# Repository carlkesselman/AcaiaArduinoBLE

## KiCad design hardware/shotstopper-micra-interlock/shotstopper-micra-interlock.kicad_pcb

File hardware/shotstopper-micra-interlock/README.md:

# ShotStopper Micra Interlock

A replacement for the ShotStopper V2.1 board, designed to give a La Marzocco
Linea Micra Linea Mini-style brew-by-weight:

- Paddle **on**: the shot starts, and the scale tares and starts its timer.
- Target weight reached: the shot **stops even though the paddle is still on**.
- Paddle **off** at any time: the shot stops, as on a stock machine.
- After an automatic stop, the next shot needs the paddle turned off and on again.
- If the board is unpowered, unplugged from the scale, or crashed, the paddle
  works exactly like a stock Micra.

Status: **design only.** The board has not been built and the firmware has
not run on hardware. Work through [Before you order](#before-you-order) first.

## Same as V2.1

The outline, the four M3 mounting holes, the Arduino Nano ESP32 position, the
two 2x8 ribbon headers (J3 "Buttons", J4 "Brain") and the 2-pin power header
are all where they are on V2.1, so the board fits the V2.1 half case and the
same place in the machine. The ribbon headers have the same pin 1 position
and every pin except the paddle pin passes straight through, so the existing
ShotStopper ribbon cables plug in the same way.

Changed from V2.1: the Nano is soldered directly into the board by its own
headers instead of sitting in sockets. That puts its top about 8 mm lower,
roughly 5–6 mm above the board instead of about 13 mm. It is still flashed
over its own USB-C port, at the board edge marked USB, or over WiFi.

Removed from V2.1: the spade terminals, the reed-switch header, and the Q1
optocoupler circuit. D9 and D11 are no longer connected.

## How it works

```
 J3 paddle pin ──JP1── PADDLE ───[ K1 normally-closed ]─── BRAIN ──JP2── J4 paddle pin
                         │                                             (to control board)
                         └──|<── D1 ── U2 LED ── R3 ── ISO 5V ┐
                                      (R6 across LED)          PS1 isolated DC-DC
 J3/J4 pin 6 (COMMON) ─────────────────────────────── ISO 0V ┘   3.3 V → 5 V
                                                                     (R4 min load)
 Nano D5  ── R1 ── K1 LED            HIGH = K1 open = machine sees paddle off
          └─ R2 10k to GND           keeps K1 closed during boot / reset
 Nano D10 ── U2 transistor to GND    LOW = paddle on  (R7 47k pull-up)
```

- **K1** (CPC1117N) is a normally-closed solid-state switch in series with the
  paddle line. Driving D5 high opens it, so the control board sees the paddle
  as off and stops the shot. With no drive, it is closed.
- **U2** senses the paddle independently of K1. A small isolated 5 V supply
  (PS1) pushes about 1.7 mA through U2's LED and D1 into the paddle wire. When
  the paddle shorts that wire to COMMON, U2 conducts and pulls D10 low. This
  works with K1 open or closed, so the firmware always knows where the paddle is.
- **D1** stops the control board's own pull-up from feeding back into the sense
  circuit. **R6** (680 Ω, smaller than R3) soaks up the leakage when the
  control board's pull-up is about 3.3 V, so a floating line doesn't read as
  "paddle on".
- **R4** (240 Ω, 1206) draws 21 mA so that PS1 has its 10 % minimum load. With
  less, its output is unspecified and can rise well above 5 V.
- The logic side (Nano) and the machine side (ribbon) share no copper. They
  connect only through K1, U2 and PS1. The minimum copper gap between the two
  sides is 0.7 mm. That is **functional isolation for a low-voltage paddle
  line, not mains-rated isolation.**

D10 has the same meaning as V2.1's "In", so the sensing is compatible.
V2.1's parallel "Out" (D11) is not on this board. The old latching mode
(`MOMENTARY false`, `PADDLE_INTERLOCK false`) still runs, but it can no longer
keep a shot going after the paddle is turned off.

## Setting the jumpers (one time, before installing)

V2.1 carried the paddle signal on ribbon pin **8** or pin **12**, depending on
the machine (its SB1–SB5 jumpers). Find out which pin yours uses, either from
your V2.1 board (which of SB1/SB2 is bridged) or with a meter. The ShotStopper
V3.1 schematic puts the Micra on pin 12 and the Linea Mini on pin 8. Then bridge
these with a blob of solder:

| Paddle on | JP1 (paddle side) | JP2 (brain side) | Also bridge |
|-----------|-------------------|------------------|-------------|
| pin 8     | centre to **8**   | centre to **8**  | JP4 (pin 12 straight through) |
| pin 12    | centre to **12**  | centre to **12** | JP3 (pin 8 straight through) |

The "8" and "12" marks are printed at the ends of JP1 and JP2. All other
ribbon pins pass straight through, and pin 6 is COMMON, as on V2.1.

## Firmware

In `examples/shotStopper/shotStopper.ino` set:

```c
#define MOMENTARY false
#define PADDLE_INTERLOCK true
```

What the firmware does in this mode:

| Event | Result |
|-------|--------|
| Paddle on | Machine brews; the shot is tracked: tare, reset and start the timer |
| Predicted target weight, or `MAX_SHOT_DURATION_S` | D5 high: K1 opens and the shot stops |
| Paddle still on after the stop | K1 stays open; no new shot |
| Paddle off (50 ms debounce, `PADDLE_DEBOUNCE_MS`) | D5 low: K1 closes, so the next paddle-on always brews |
| Paddle off before the target | Shot stops; K1 never opens |
| Scale lost during a weighed shot | D5 high: the shot stops (`STOP_ON_SCALE_LOSS`; set it `false` to leave the shot to the paddle) |
| Scale not connected when the paddle goes on | K1 stays closed; the paddle works by hand |
| Paddle on for `INTERLOCK_MAX_BREW_S` (90 s), with or without a scale | D5 high: the brew stops until the paddle is off |
| Reconnect, or reset, partway through a shot | The shot keeps running on the paddle and isn't re-tared |
| Crash or watchdog reset during a held stop | The stop stays held until the paddle is off, so a finished shot isn't restarted |
| `loop()` stalls for 20 s (`WATCHDOG_S`) | The watchdog resets the board, and K1 closes |

### Fail-safe guarantees

- **Paddle off always stops brewing.** This is enforced by hardware: K1 is in
  series, so an open paddle opens the line whatever the ESP32 does.
- **Board unpowered, unplugged, or held in reset.** K1 is normally closed, and R2
  keeps it closed while D5 is undriven, so the Micra behaves as stock.
- **Paddle on starts brewing** whenever the firmware is running, or the board is
  off or resetting. The only time it doesn't is an automatic stop being held,
  and that hold ends as soon as the paddle reads off. A hung ESP32 is reset by
  the watchdog within `WATCHDOG_S`.
- **No remote start.** The ESP32 can only interrupt the paddle line. It cannot
  make the machine brew.

These cases are covered by host tests with stub libraries, not on hardware.

Flow rate, the scale sanity checks and over-the-air updates are described
in [`examples/shotStopper/README.md`](../../examples/shotStopper/README.md).

## Ordering from PCBWay

Everything is in `fab/`:

| File | Upload as |
|------|-----------|
| `shotstopper-micra-interlock-gerbers.zip` | PCB Gerber files (includes drill files) |
| `bom.csv` | Assembly BOM (manufacturer part numbers) |
| `centroid.csv` | Pick-and-place / centroid file (mm, top side) |

PCB options: 2 layers, 44.3 × 41.3 mm, 1.6 mm FR-4, 1 oz copper, any
solder-mask colour, lead-free HASL or ENIG. Minimum track and gap are
0.25 mm and 0.2 mm, and the smallest drill is 0.3 mm (vias), all inside
PCBWay's standard capability.

Assembly: top side only, SMD and through-hole. The Arduino Nano ESP32 *with
headers* (Arduino ABX00092) is on the BOM as J1: PCBWay solders its two pin
rows straight into the J1 and J2 holes, with no sockets, USB-C toward the
edge marked USB. J2 is the Nano's second row, not a separate part, so it is
not on the BOM or in the centroid file. JP1–JP4 are bare pads with no part
to place.

## Before you order

1. **Paddle line voltage and current.** With the machine on, measure DC volts
   between the paddle ribbon wire and pin 6 (COMMON), with the paddle off; expect
   3.3–5 V. Then measure the current with the paddle on; expect a few mA. K1 is
   rated 60 V / 120 mA. The line must not be mains.
2. **Which ribbon pin** carries the paddle (8 or 12). See the jumper table above.
3. **PS1 pinout.** The footprint assumes the industry-standard SIP-4 (1 = Vin−,
   2 = Vin+, 3 = Vout−, 4 = Vout+), which Mornsun B0305S-1WR3 and Murata MEE1S0305SC
   both use. Check it against the current datasheet.
4. **Clearance.** PS1 is about 10 mm tall and sits beside J4 (bottom right).
   Check that it clears whatever is above the board in your machine.
5. **First power-up on the bench.** With only USB connected, check that D5 high
   makes K1 open: measure the resistance between J3 and J4 on the selected pin.
   Then check that shorting the selected J3 pin to pin 6 pulls D10 low.
   Measure across C2 as well: expect 5.0–5.5 V from PS1.

Work inside the Micra only with it unplugged. Mains is present in the chassis.

## Regenerating the board

`design.py` is the source of truth: parts, positions, nets, and the
logic/machine routing areas.

```bash
./make_all.sh /path/to/python-with-numpy-scipy-pillow
```

The script runs `build_board.py` (KiCad Python: places the parts),
`route.py` (a small two-layer router that keeps each net on its own side),
`finish_board.py` (adds tracks and silkscreen), KiCad DRC, and the
Gerber/drill/BOM/centroid exports. It needs KiCad 10. You can open
`shotstopper-micra-interlock.kicad_pcb` in KiCad and edit it by hand, but a
rerun of the script overwrites it.

There is no schematic file. The netlist is in `design.py` (`NETS`).

Based on ShotStopper V2.1 by Tate Mazer (MIT License).

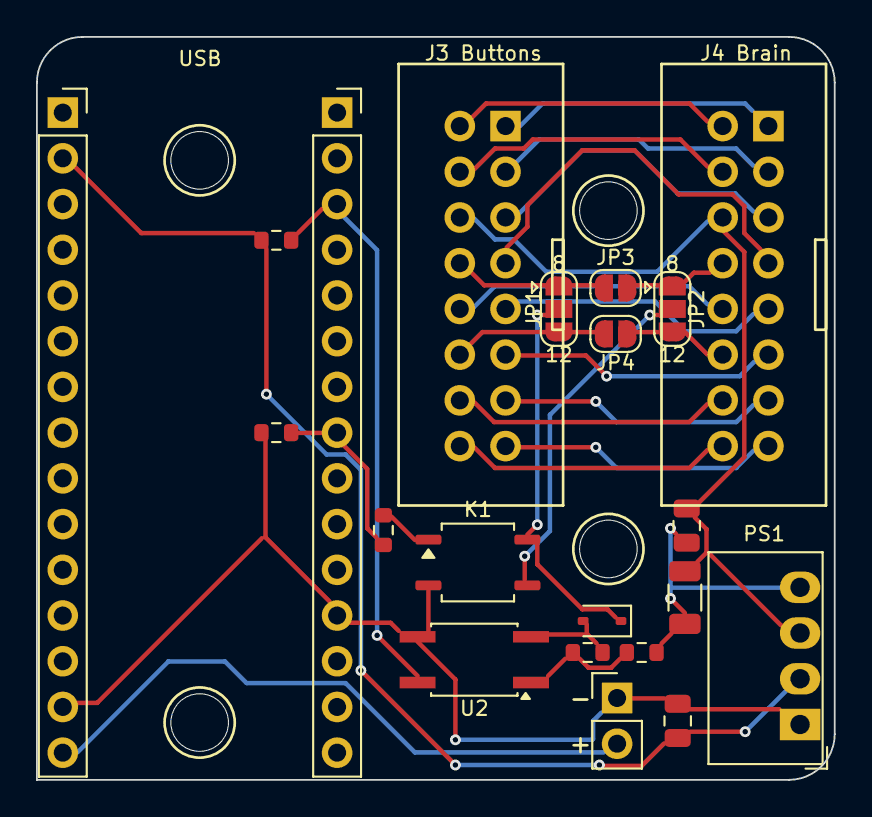
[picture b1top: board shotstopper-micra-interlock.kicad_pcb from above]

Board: 2 copper layers, 44.3 x 41.3 mm, 25 parts (0 on the bottom side), 29 nets.

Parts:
C1, C2: 4.7u; C_0805_2012Metric
D1: 1N4148WS; D_SOD-323
H1, H2, H3, H4: MountingHole_3.2mm_M3_Standoff
J1: Nano ESP32; PinSocket_1x15_P2.54mm_Vertical
J2: Nano ESP32 R row; PinSocket_1x15_P2.54mm_Vertical
J3: Buttons; Ribbon_2x08_P2.54mm_V2.1
J4: Brain; Ribbon_2x08_P2.54mm_V2.1
J5: PWR; PinHeader_1x02_P2.54mm_Vertical
JP1: PADDLE 8|12; SolderJumper-3_P1.3mm_Open_RoundedPad1.0x1.5mm
JP2: BRAIN 8|12; SolderJumper-3_P1.3mm_Open_RoundedPad1.0x1.5mm
JP3: 8 THRU; SolderJumper-2_P1.3mm_Open_RoundedPad1.0x1.5mm
JP4: 12 THRU; SolderJumper-2_P1.3mm_Open_RoundedPad1.0x1.5mm
K1: CPC1117N; SOP-4_3.8x4.1mm_P2.54mm
PS1: B0305S-1WR3; Converter_DCDC_Murata_MEE1SxxxxSC_THT
R1: 390; R_0603_1608Metric
R2: 10k; R_0603_1608Metric
R3: 1k; R_0603_1608Metric
R4: 240; R_1206_3216Metric
R6: 680; R_0603_1608Metric
R7: 47k; R_0603_1608Metric
U2: EL357N; SO-4_4.4x3.6mm_P2.54mm

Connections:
+3V3: C1.1, J1.2, PS1.2, R7.1
BRAIN: JP2.2, K1.3
COMMON: C2.2, J3.6, J4.6, PS1.3, R4.2
GND: C1.2, J1.14, J2.12, J5.1, K1.2, PS1.1, R2.1, U2.3
ISO5V: C2.1, PS1.4, R3.2, R4.1
K1_A: K1.1, R1.2
PADDLE: D1.1, JP1.2, K1.4
RIB1: J3.1, J4.1
RIB2: J3.2, J4.2
RIB3: J3.3, J4.3
RIB4: J3.4, J4.4
RIB5: J3.5, J4.5
RIB7: J3.7, J4.7
RIB8_B: J4.8, JP2.1, JP3.2
RIB8_P: J3.8, JP1.1, JP3.1
RIB9: J3.9, J4.9
RIB10: J3.10, J4.10
RIB11: J3.11, J4.11
RIB12_B: J4.12, JP2.3, JP4.2
RIB12_P: J3.12, JP1.3, JP4.1
RIB13: J3.13, J4.13
RIB14: J3.14, J4.14
RIB15: J3.15, J4.15
RIB16: J3.16, J4.16
SENSE: J2.3, R7.2, U2.4
STOP: J2.8, R1.1, R2.2
U2_A: R3.1, R6.1, U2.1
U2_K: D1.2, R6.2, U2.2
VIN: J1.15, J5.2

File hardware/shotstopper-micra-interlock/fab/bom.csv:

Item,Designator,Qty,Manufacturer,Mfg Part #,Description / Value,Package/Footprint,Type,Notes
1,J1,1,Arduino,ABX00092,Nano ESP32 - Arduino Nano ESP32 with headers (left pin row; right row in J2),PinSocket_1x15_P2.54mm_Vertical,Thru-hole,"One module, two pin rows: J1 = left row (pin 1 = D13), J2 = right row (pin 1 = D12). USB-C toward the board edge marked USB. Solder the Nano's headers directly into J1 and J2, seated flat; NO sockets"
2,J3,1,Sullins,PEC08DAAN,Buttons - Male header 2x8 2.54mm (paddle ribbon),Ribbon_2x08,Thru-hole,Mount on TOP side
3,J4,1,Sullins,PEC08DAAN,Brain - Male header 2x8 2.54mm (control board ribbon),Ribbon_2x08,Thru-hole,
4,J5,1,Sullins,PEC02SAAN,"PWR - Male header 1x2 2.54mm (+ = VIN, - = GND)",PinHeader_1x02_P2.54mm_Vertical,Thru-hole,
5,K1,1,Littelfuse,CPC1117NTR,CPC1117N - OptoMOS relay 1-Form-B (normally closed) 60V 120mA,SOP-4_3.8x4.1mm_P2.54mm,SMD,Normally-CLOSED type; do not substitute a normally-open relay
6,U2,1,Everlight,EL357N(C)(TA)-G,"EL357N - Optocoupler, paddle sense",SO-4_4.4x3.6mm_P2.54mm,SMD,
7,PS1,1,Mornsun,B0305S-1WR3,B0305S-1WR3 - Isolated DC-DC 3.3V->5V 1W SIP-4,Converter_DCDC_Murata_MEE1SxxxxSC_THT,Thru-hole,Through-hole SIP-4; Murata MEE1S0305SC is a pin-compatible alternative
8,D1,1,Diodes Inc,1N4148WS-7-F,1N4148WS - Signal diode,D_SOD-323,SMD,
9,R1,1,Yageo,RC0603FR-07390RL,390 - K1 LED current,R_0603_1608Metric,SMD,
10,R2,1,Yageo,RC0603FR-0710KL,10k - K1 pull-down (closed in reset),R_0603_1608Metric,SMD,
11,R3,1,Yageo,RC0603FR-071KL,1k - Paddle sense current,R_0603_1608Metric,SMD,
12,R4,1,Yageo,RC1206FR-07240RL,240 - DC-DC minimum load (0.25 W),R_1206_3216Metric,SMD,
13,R6,1,Yageo,RC0603FR-07680RL,680 - U2 LED leakage shunt,R_0603_1608Metric,SMD,
14,R7,1,Yageo,RC0603FR-0747KL,47k - Paddle sense pull-up,R_0603_1608Metric,SMD,
15,"C1,C2",2,Samsung,CL21A475KAQNNNE,4.7u - DC-DC decoupling,C_0805_2012Metric,SMD,
